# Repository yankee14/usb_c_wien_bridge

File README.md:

# USB C Wien Bridge Oscillator

Generates an approx. 1 V<sub>p-p</sub> sine @ approx 700 Hz. Power via USB C. Pin header output to next PCB.

For use in a morse code CW telegraph key network.

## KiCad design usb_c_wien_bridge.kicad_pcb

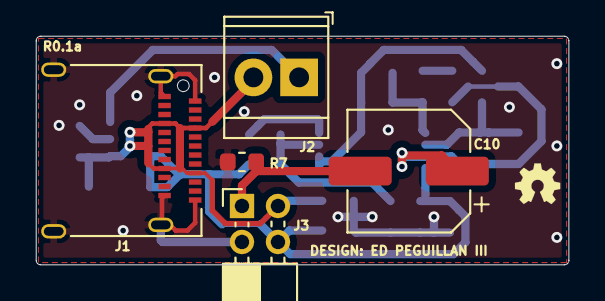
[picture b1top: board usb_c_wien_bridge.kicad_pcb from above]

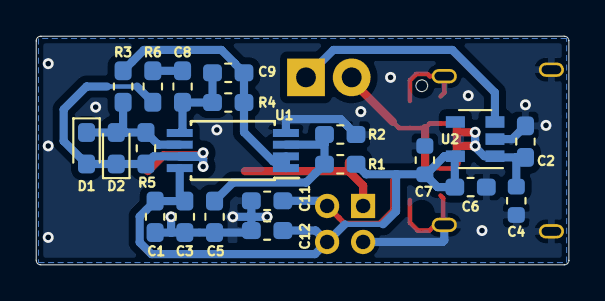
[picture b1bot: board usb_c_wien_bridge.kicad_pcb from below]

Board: 2 copper layers, 29.6 x 12.7 mm, 26 parts (21 on the bottom side), 11 nets.

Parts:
C1, C5: 0u1F; C_0603_1608Metric_Pad1.05x0.95mm_HandSolder
C2, C3, C6, C11, C12: 1uF; C_0603_1608Metric_Pad1.05x0.95mm_HandSolder
C4, C7: 0u1F; C_0603_1608Metric
C8, C9: 1nF; C_0603_1608Metric_Pad1.05x0.95mm_HandSolder
C10: 47uF; CP_Elec_6.3x5.4_Nichicon
D1, D2: LED; LED_0603_1608Metric_Pad1.05x0.95mm_HandSolder
J1: USB_C_Receptacle_USB2.0; USB_C_Receptacle_Amphenol_12401610E4-2A
J2: Screw_Terminal_01x02; TerminalBlock_TE_282834-2_1x02_P2.54mm_Horizontal
J3: Conn_02x02; PinSocket_2x02_P2.00mm_Horizontal
R1, R2, R3: 100k; R_0603_1608Metric_Pad1.05x0.95mm_HandSolder
R4, R5, R6: 220k; R_0603_1608Metric_Pad1.05x0.95mm_HandSolder
R7: 100k; R_0603_1608Metric
U1: LMV358; TSSOP-8_4.4x3mm_P0.65mm
U2: MIC5504-3.3YM5; SOT-23-5

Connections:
+3V3: C1.1, C3.1, C6.1, C7.1, C12.1, J3.4, R1.1, U1.8, U2.5
+5V0: C2.1, C4.1, C11.1, J1.A4, J1.A9, J1.B4, J1.B9, J2.2, J3.3, U2.1
/A_OUT: C10.2, J3.1, R7.1
/NEG_FB: D1.1, D2.2, R3.1, R5.2, U1.6
/POS_FB: C8.2, C9.2, R4.1, U1.5
/RAIL_SPLIT: C9.1, R3.2, R4.2, U1.1, U1.2
/V_DIV: C5.1, R1.2, R2.1, U1.3
GNDA: C1.2, C2.2, C3.2, C4.2, C5.2, C6.2, C7.2, C11.2, C12.2, J1.A1, J1.A12, J1.B1, J1.B12, J1.S1, J3.2, R2.2, R7.2, U1.4, U2.2
unnamed: C8.1, R6.2
unnamed: C10.1, D1.2, D2.1, R5.1, R6.1, U1.7
unnamed: J2.1, U2.3

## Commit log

2019-03-25 Schematic mostly complete
2019-03-26 Add:
    1. 1x2, 2.54 mm, screw terminal for connecting telegraph key to LDO enable.
    2. LDO for 3.3 V.
    3. 2x2, 2.00 mm, female unshrouded pin socket for board connection
2019-03-29 Place all components. Needs routing.
2019-04-01 Finish routing
2019-04-01 Add vias to ground islands
2019-04-01 * 10 mil fillet edge cuts corners * 10 mil fillet front and back GND zones * Shrink board
2019-04-01 Fix silkcsreen designator sizes and position
2019-04-01 Add revision number to PCB
2019-04-01 Generate gerbers
